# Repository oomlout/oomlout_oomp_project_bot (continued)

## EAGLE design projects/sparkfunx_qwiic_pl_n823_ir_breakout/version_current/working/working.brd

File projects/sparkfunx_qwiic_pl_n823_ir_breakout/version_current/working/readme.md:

# OOMP Project  
## Qwiic_PL-N823_IR_Breakout  by sparkfunX  
  
oomp key: oomp_projects_flat_sparkfunx_qwiic_pl_n823_ir_breakout  
(snippet of original readme)  
  
SparkFun Qwiic PL-N823 IR Breakout  
===================================  

[*SparkFun Qwiic IR Breakout (SPX-15804)*](https://www.sparkfun.com/products/15804)  
  
PL-N823-01 Lensless IR Sensor breakout with signal amplifier and I2C ADC   
  
This board allows for digital sensor reading of IR signals from external sources. One such application can be the detection of heat given off by the human body. Operating voltage is 5V for the board as a whole, and while under 1mm thick materials detection can be as far away as 10cm to 20cm.  
  
Repository Contents  
-------------------  
  
* **/Documents** - Contains datasheets  
* **/Hardware** - Current .brd and .sch files for product  
  
Documentation  
-------------  
  
* **[Installing an Arduino Library Guide](https://learn.sparkfun.com/tutorials/installing-an-arduino-library)** - Basic information on how to install an Arduino library.  
  
License Information  
-------------------  
  
This product is _**open source**_!  
  
Please review the LICENSE.md file for license information.  
  
If you have any questions or concerns on licensing, please contact technical support on our [SparkFun forums](https://forum.sparkfun.com/viewforum.php?f=152).  
  
Distributed as-is; no warranty is given.  
  
- Your friends at SparkFun.  
  
_<COLLABORATION CREDIT>_  
  
  full source readme at [readme_src.md](readme_src.md)  
  
source repo at: [https://github.com/sparkfunX/Qwiic_PL-N823_IR_Breakout](https://github.com/sparkfunX/Qwiic_PL-N823_IR_Breakout)  
## Board  

## Schematic  

[schematic pdf](working_schematic.pdf)  
## Images

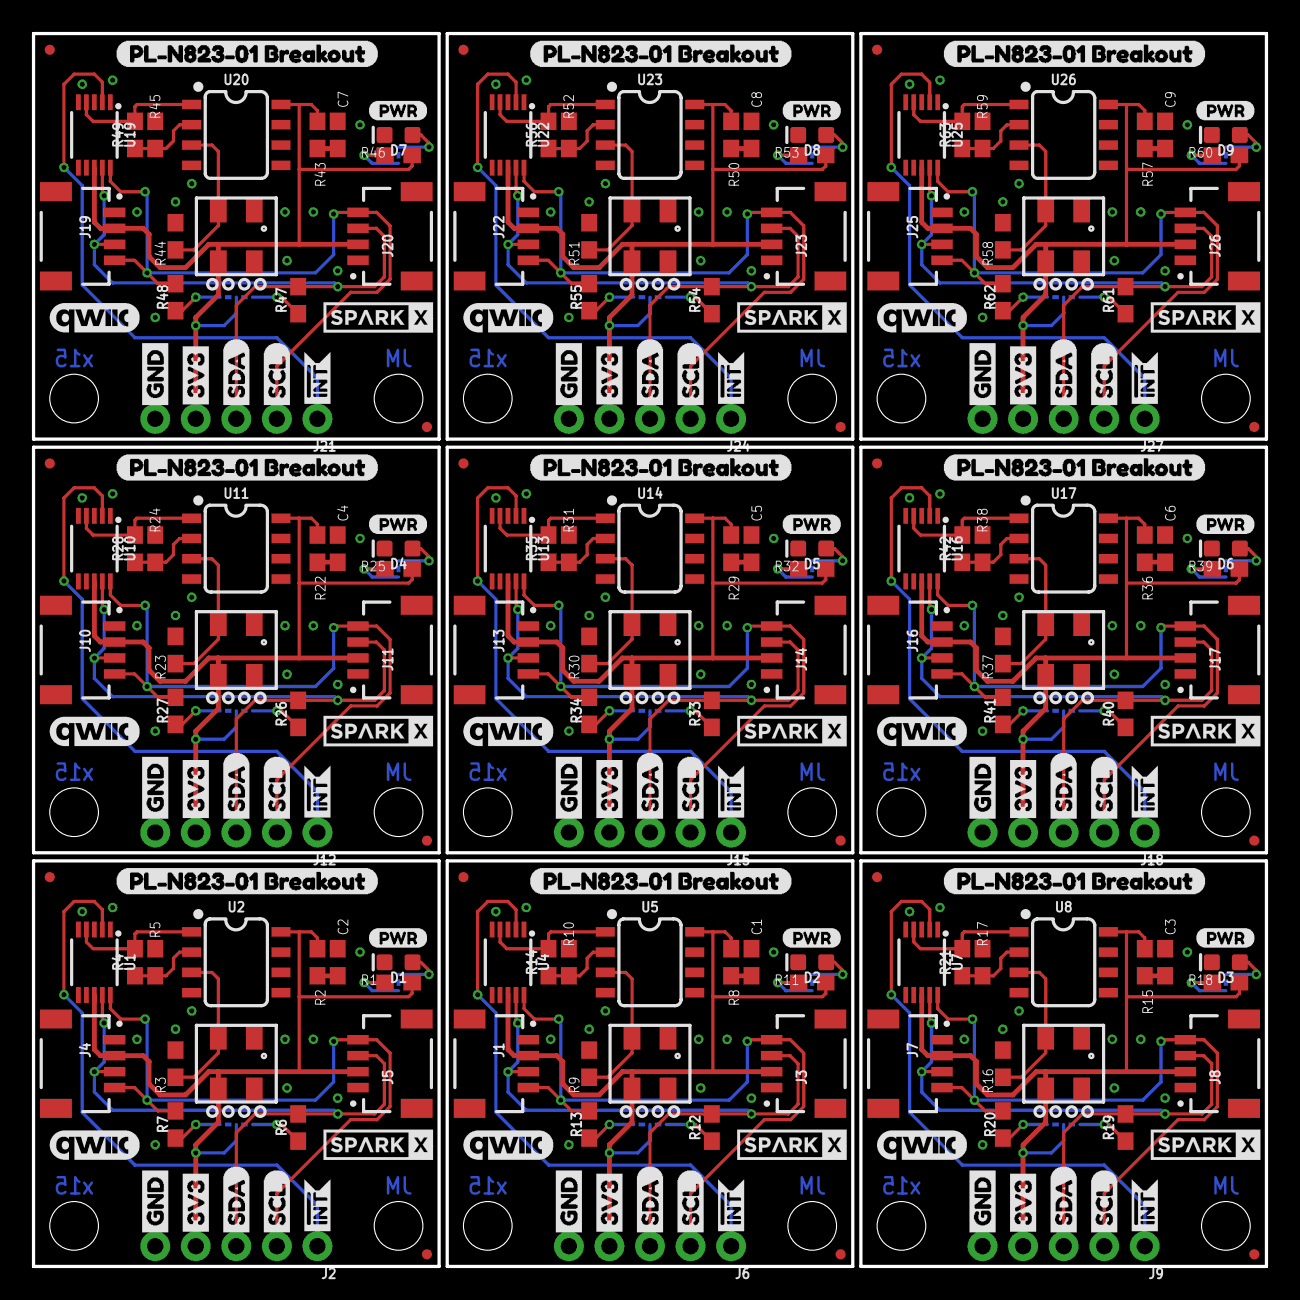
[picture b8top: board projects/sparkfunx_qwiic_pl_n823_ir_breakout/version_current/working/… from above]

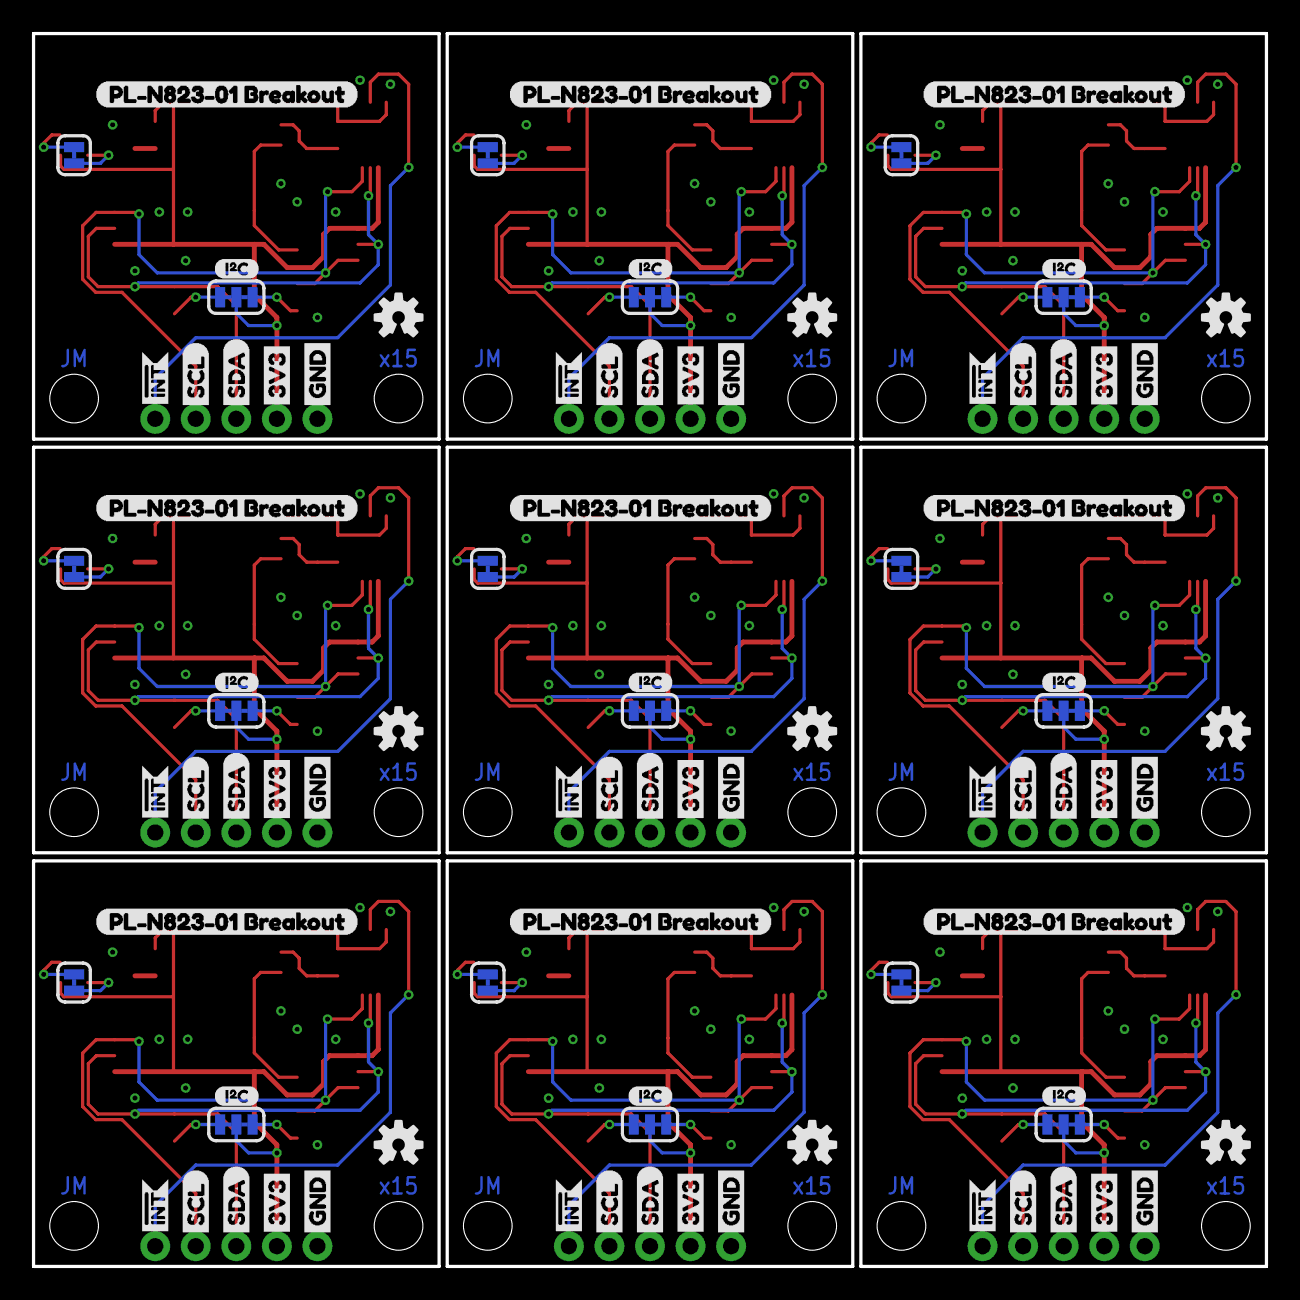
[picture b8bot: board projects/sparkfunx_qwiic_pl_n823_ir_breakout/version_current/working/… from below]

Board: 2 copper layers, 77.2 x 77.2 mm, 360 parts (90 on the bottom side), 117 nets.

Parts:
C1, C2, C3, C4, C5, C6, C7, C8, C9: 0.1uF; 0603
D1, D2, D3, D4, D5, D6, D7, D8, D9: BLUE; LED-0603
FD1, FD2, FD3, FD4, FD5, FD6, FD7, FD8, FD9, FD10, FD11, FD12, FD13, FD14, FD15, FD16, FD17, FD18: FIDUCIALUFIDUCIAL; FIDUCIAL-MICRO
FRAME1, FRAME2, FRAME3, FRAME4, FRAME5, FRAME6, FRAME7, FRAME8, FRAME9: FRAME-LETTERNO_PACKAGE; DUMMY
H1, H2, H3, H4, H5, H6, H7, H8, H9, H10, H11, H12, H13, H14, H15, H16, H17, H18: STAND-OFFTIGHT; STAND-OFF-TIGHT
J1, J3, J4, J5, J7, J8, J10, J11, J13, J14, J16, J17, J19, J20, J22, J23, J25, J26: JST04_1MM_RA
J2, J6, J9, J12, J15, J18, J21, J24, J27: 1X05_NO_SILK
JP1, JP3, JP5, JP7, JP9, JP11, JP13, JP15, JP17: JUMPER-SMT_3_2-NC_TRACE_SILK; SMT-JUMPER_3_2-NC_TRACE_SILK
JP2, JP4, JP6, JP8, JP10, JP12, JP14, JP16, JP18: JUMPER-SMT_2_NC_TRACE_SILK; SMT-JUMPER_2_NC_TRACE_SILK
R1, R11, R18, R25, R32, R39, R46, R53, R60: 27; 0603
R2, R8, R15, R22, R29, R36, R43, R50, R57: 10k; 0603
R3, R9, R16, R23, R30, R37, R44, R51, R58: 47k; 0603
R4, R14, R21, R28, R35, R42, R49, R56, R63: 1.20k; 0603
R5, R10, R17, R24, R31, R38, R45, R52, R59: 1k; 0603
R6, R7, R12, R13, R19, R20, R26, R27, R33, R34, R40, R41, R47, R48, R54, R55, R61, R62: 2.2k; 0603
U1, U4, U7, U10, U13, U16, U19, U22, U25: ADS1015; MSOP10
U2, U5, U8, U11, U14, U17, U20, U23, U26: LMV358; SO08
U3, U6, U9, U12, U15, U18, U21, U24, U27: PL-N823-01
U$1, U$22, U$40, U$58, U$76, U$94, U$112, U$130, U$148: QWIIC_COPYRIGHT_SMALL
U$2, U$13, U$24, U$26, U$42, U$44, U$60, U$62, U$78, U$80, U$96, U$98, U$114, U$116, U$132, U$134, U$150, U$152: SDA-[)
U$3, U$36, U$54, U$72, U$90, U$108, U$126, U$144, U$162: PRODUCTION_INSTRUCTIONS
U$4, U$8, U$20, U$32, U$38, U$50, U$56, U$68, U$74, U$86, U$92, U$104, U$110, U$122, U$128, U$140, U$146, U$158: PL#N823#01_BREAKOUT0
U$5, U$33, U$51, U$69, U$87, U$105, U$123, U$141, U$159: I_SUPER2_C-()-03
U$6, U$11, U$34, U$35, U$52, U$53, U$70, U$71, U$88, U$89, U$106, U$107, U$124, U$125, U$142, U$143, U$160, U$161: INT#-[<-04
U$7, U$19, U$37, U$55, U$73, U$91, U$109, U$127, U$145: OSHW-LOGO-S
U$9, U$23, U$41, U$59, U$77, U$95, U$113, U$131, U$149: PWR-()-03
U$10, U$21, U$39, U$57, U$75, U$93, U$111, U$129, U$147: SPARKX-SMALL
U$12, U$14, U$25, U$27, U$43, U$45, U$61, U$63, U$79, U$81, U$97, U$99, U$115, U$117, U$133, U$135, U$151, U$153: SCL-[)
U$15, U$16, U$28, U$29, U$46, U$47, U$64, U$65, U$82, U$83, U$100, U$101, U$118, U$119, U$136, U$137, U$154, U$155: 3V3-04
U$17, U$18, U$30, U$31, U$48, U$49, U$66, U$67, U$84, U$85, U$102, U$103, U$120, U$121, U$138, U$139, U$156, U$157: GND-04

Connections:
3.3V: J2.4, J4.2, J5.2, JP1.2, R1.2, R2.1, U1.8, U2.8, U3.DRAIN
3.3V1: J1.2, J3.2, J6.4, JP3.2, R8.1, R11.2, U4.8, U5.8, U6.DRAIN
3.3V2: J7.2, J8.2, J9.4, JP5.2, R15.1, R18.2, U7.8, U8.8, U9.DRAIN
3.3V3: J10.2, J11.2, J12.4, JP7.2, R22.1, R25.2, U10.8, U11.8, U12.DRAIN
3.3V4: J13.2, J14.2, J15.4, JP9.2, R29.1, R32.2, U13.8, U14.8, U15.DRAIN
3.3V5: J16.2, J17.2, J18.4, JP11.2, R36.1, R39.2, U16.8, U17.8, U18.DRAIN
3.3V6: J19.2, J20.2, J21.4, JP13.2, R43.1, R46.2, U19.8, U20.8, U21.DRAIN
3.3V7: J22.2, J23.2, J24.4, JP15.2, R50.1, R53.2, U22.8, U23.8, U24.DRAIN
3.3V8: J25.2, J26.2, J27.4, JP17.2, R57.1, R60.2, U25.8, U26.8, U27.DRAIN
!INT: J2.1, U1.2
!INT1: J6.1, U4.2
!INT2: J9.1, U7.2
!INT3: J12.1, U10.2
!INT4: J15.1, U13.2
!INT5: J18.1, U16.2
!INT6: J21.1, U19.2
!INT7: J24.1, U22.2
!INT8: J27.1, U25.2
GND: C2.2, D1.C, J2.5, J4.1, J5.1, R3.2, R5.1, U1.1, U1.3, U2.4, U3.GND@1, U3.GND@2
GND1: C1.2, D2.C, J1.1, J3.1, J6.5, R9.2, R10.1, U4.1, U4.3, U5.4, U6.GND@1, U6.GND@2
GND2: C3.2, D3.C, J7.1, J8.1, J9.5, R16.2, R17.1, U7.1, U7.3, U8.4, U9.GND@1, U9.GND@2
GND3: C4.2, D4.C, J10.1, J11.1, J12.5, R23.2, R24.1, U10.1, U10.3, U11.4, U12.GND@1, U12.GND@2
GND4: C5.2, D5.C, J13.1, J14.1, J15.5, R30.2, R31.1, U13.1, U13.3, U14.4, U15.GND@1, U15.GND@2
GND5: C6.2, D6.C, J16.1, J17.1, J18.5, R37.2, R38.1, U16.1, U16.3, U17.4, U18.GND@1, U18.GND@2
GND6: C7.2, D7.C, J19.1, J20.1, J21.5, R44.2, R45.1, U19.1, U19.3, U20.4, U21.GND@1, U21.GND@2
GND7: C8.2, D8.C, J22.1, J23.1, J24.5, R51.2, R52.1, U22.1, U22.3, U23.4, U24.GND@1, U24.GND@2
GND8: C9.2, D9.C, J25.1, J26.1, J27.5, R58.2, R59.1, U25.1, U25.3, U26.4, U27.GND@1, U27.GND@2
unnamed: R4.1, R5.2, U2.2
unnamed: C2.1, R2.2
unnamed: JP2.1, R1.1
unnamed: JP1.3, R7.1
unnamed: JP1.1, R6.1
unnamed: D1.A, JP2.2
unnamed: C1.1, R8.2
unnamed: R10.2, R14.1, U5.2
unnamed: JP3.3, R13.1
unnamed: JP3.1, R12.1
unnamed: D2.A, JP4.2
unnamed: JP4.1, R11.1
unnamed: C3.1, R15.2
unnamed: R17.2, R21.1, U8.2
unnamed: JP5.3, R20.1
unnamed: JP5.1, R19.1
unnamed: D3.A, JP6.2
unnamed: JP6.1, R18.1
unnamed: C4.1, R22.2
unnamed: R24.2, R28.1, U11.2
unnamed: JP7.3, R27.1
unnamed: JP7.1, R26.1
unnamed: D4.A, JP8.2
unnamed: JP8.1, R25.1
unnamed: C5.1, R29.2
unnamed: R31.2, R35.1, U14.2
unnamed: JP9.3, R34.1
unnamed: JP9.1, R33.1
unnamed: D5.A, JP10.2
unnamed: JP10.1, R32.1
unnamed: C6.1, R36.2
unnamed: R38.2, R42.1, U17.2
unnamed: JP11.3, R41.1
unnamed: JP11.1, R40.1
unnamed: D6.A, JP12.2
unnamed: JP12.1, R39.1
unnamed: C7.1, R43.2
unnamed: R45.2, R49.1, U20.2
unnamed: JP13.3, R48.1
unnamed: JP13.1, R47.1
unnamed: D7.A, JP14.2
unnamed: JP14.1, R46.1
unnamed: C8.1, R50.2
unnamed: R52.2, R56.1, U23.2
unnamed: JP15.3, R55.1
unnamed: JP15.1, R54.1
unnamed: D8.A, JP16.2
unnamed: JP16.1, R53.1
unnamed: C9.1, R57.2
unnamed: R59.2, R63.1, U26.2
unnamed: JP17.3, R62.1
unnamed: JP17.1, R61.1
unnamed: D9.A, JP18.2
unnamed: JP18.1, R60.1
SCL: J2.2, J4.4, J5.4, R7.2, U1.10
SCL1: J1.4, J3.4, J6.2, R13.2, U4.10
SCL2: J7.4, J8.4, J9.2, R20.2, U7.10
SCL3: J10.4, J11.4, J12.2, R27.2, U10.10
SCL4: J13.4, J14.4, J15.2, R34.2, U13.10
SCL5: J16.4, J17.4, J18.2, R41.2, U16.10
SCL6: J19.4, J20.4, J21.2, R48.2, U19.10
SCL7: J22.4, J23.4, J24.2, R55.2, U22.10
SCL8: J25.4, J26.4, J27.2, R62.2, U25.10
SDA: J2.3, J4.3, J5.3, R6.2, U1.9
SDA1: J1.3, J3.3, J6.3, R12.2, U4.9
SDA2: J7.3, J8.3, J9.3, R19.2, U7.9
SDA3: J10.3, J11.3, J12.3, R26.2, U10.9
SDA4: J13.3, J14.3, J15.3, R33.2, U13.9
SDA5: J16.3, J17.3, J18.3, R40.2, U16.9
SDA6: J19.3, J20.3, J21.3, R47.2, U19.9
SDA7: J22.3, J23.3, J24.3, R54.2, U22.9
SDA8: J25.3, J26.3, J27.3, R61.2, U25.9
SIGNAL: R4.2, U1.4, U2.1
SIGNAL1: R14.2, U4.4, U5.1
SIGNAL2: R21.2, U7.4, U8.1
SIGNAL3: R28.2, U10.4, U11.1
SIGNAL4: R35.2, U13.4, U14.1
SIGNAL5: R42.2, U16.4, U17.1
SIGNAL6: R49.2, U19.4, U20.1
SIGNAL7: R56.2, U22.4, U23.1
SIGNAL8: R63.2, U25.4, U26.1
SOURCE: R3.1, U2.3, U3.SOURCE
SOURCE1: R9.1, U5.3, U6.SOURCE
SOURCE2: R16.1, U8.3, U9.SOURCE
SOURCE3: R23.1, U11.3, U12.SOURCE
SOURCE4: R30.1, U14.3, U15.SOURCE
SOURCE5: R37.1, U17.3, U18.SOURCE
SOURCE6: R44.1, U20.3, U21.SOURCE
SOURCE7: R51.1, U23.3, U24.SOURCE
SOURCE8: R58.1, U26.3, U27.SOURCE

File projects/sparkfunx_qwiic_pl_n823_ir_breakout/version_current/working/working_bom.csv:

"Id";"Designator";"Footprint";"Quantity";"Designation";"Supplier and ref";
1;"U14,U11,U23,U5,U20,U17,U2,U26,U8";"SO08";9;"LMV358";;;
2;"J27,J2,J9,J6,J18,J12,J21,J24,J15";"1X05_NO_SILK";9;"";;;
3;"U$66,U$30,U$156,U$48,U$102,U$84,U$17,U$120,U$138,U$85,U$139,U$157,U$18,U$31,U$49,U$121,U$103,U$67";"GND-04";18;"";;;
4;"R59,R38,R24,R5,R45,R52,R10,R17,R31";"0603";9;"1k";;;
5;"C1,C3,C4,C7,C9,C2,C6,C5,C8";"0603";9;"0.1uF";;;
6;"U21,U15,U3,U27,U9,U18,U24,U6,U12";"PL-N823-01";9;"PL-N823-01";;;
7;"U$39,U$93,U$57,U$10,U$111,U$147,U$21,U$75,U$129";"SPARKX-SMALL";9;"";;;
8;"R14,R21,R63,R35,R49,R28,R56,R4,R42";"0603";9;"1.20k";;;
9;"R37,R58,R51,R16,R23,R44,R30,R3,R9";"0603";9;"47k";;;
10;"J1,J10,J25,J20,J13,J22,J3,J8,J17,J5,J4,J7,J16,J23,J19,J11,J14,J26";"JST04_1MM_RA";18;"";;;
11;"H15,H16,H12,H2,H8,H6,H3,H18,H11,H5,H17,H9,H7,H13,H10,H14,H4,H1";"STAND-OFF-TIGHT";18;"STAND-OFFTIGHT";;;
12;"D8,D1,D9,D2,D4,D6,D7,D3,D5";"LED-0603";9;"BLUE";;;
13;"R13,R19,R40,R26,R6,R48,R61,R54,R7,R47,R41,R55,R33,R27,R34,R20,R12,R62";"0603";18;"2.2k";;;
14;"U$136,U$154,U$118,U$15,U$82,U$64,U$100,U$28,U$46,U$155,U$65,U$16,U$29,U$137,U$101,U$119,U$47,U$83";"3V3-04";18;"";;;
15;"FRAME6,FRAME2,FRAME7,FRAME1,FRAME5,FRAME4,FRAME8,FRAME3,FRAME9";"DUMMY";9;"FRAME-LETTERNO_PACKAGE";;;
16;"U$94,U$112,U$76,U$22,U$148,U$1,U$130,U$40,U$58";"QWIIC_COPYRIGHT_SMALL";9;"";;;
17;"R25,R53,R60,R39,R32,R11,R18,R1,R46";"0603";9;"27";;;
18;"U$3,U$162,U$126,U$54,U$108,U$36,U$90,U$72,U$144";"PRODUCTION_INSTRUCTIONS";9;"";;;
19;"R8,R50,R15,R43,R36,R22,R29,R57,R2";"0603";9;"10k";;;
20;"U1,U22,U13,U19,U16,U25,U7,U4,U10";"MSOP10";9;"ADS1015";;;
21;"FD5,FD10,FD6,FD8,FD15,FD4,FD17,FD13,FD2,FD11,FD16,FD9,FD18,FD14,FD12,FD3,FD7,FD1";"FIDUCIAL-MICRO";18;"FIDUCIALUFIDUCIAL";;;
22;"U$79,U$61,U$43,U$133,U$25,U$115,U$97,U$151,U$12,U$45,U$135,U$14,U$99,U$63,U$27,U$81,U$153,U$117";"SCL-[)";18;"";;;
23;"U$113,U$41,U$9,U$23,U$95,U$59,U$149,U$131,U$77";"PWR-()-03";9;"";;;
24;"U$74,U$8,U$20,U$146,U$38,U$56,U$128,U$110,U$92,U$104,U$158,U$68,U$86,U$140,U$32,U$50,U$122,U$4";"PL#N823#01_BREAKOUT0";18;"";;;
25;"U$34,U$106,U$52,U$88,U$70,U$6,U$142,U$160,U$124,U$143,U$107,U$125,U$35,U$71,U$53,U$161,U$89,U$11";"INT#-[_-04";18;"";;;
26;"U$150,U$78,U$24,U$132,U$60,U$114,U$2,U$96,U$42,U$116,U$44,U$98,U$152,U$13,U$62,U$26,U$80,U$134";"SDA-[)";18;"";;;
27;"U$55,U$7,U$19,U$127,U$145,U$91,U$73,U$109,U$37";"OSHW-LOGO-S";9;"";;;
28;"JP6,JP8,JP2,JP10,JP12,JP4,JP16,JP18,JP14";"SMT-JUMPER_2_NC_TRACE_SILK";9;"JUMPER-SMT_2_NC_TRACE_SILK";;;
29;"U$5,U$105,U$123,U$69,U$87,U$159,U$33,U$51,U$141";"I_SUPER2_C-()-03";9;"";;;
30;"JP3,JP1,JP13,JP11,JP7,JP15,JP9,JP5,JP17";"SMT-JUMPER_3_2-NC_TRACE_SILK";9;"JUMPER-SMT_3_2-NC_TRACE_SILK";;;
